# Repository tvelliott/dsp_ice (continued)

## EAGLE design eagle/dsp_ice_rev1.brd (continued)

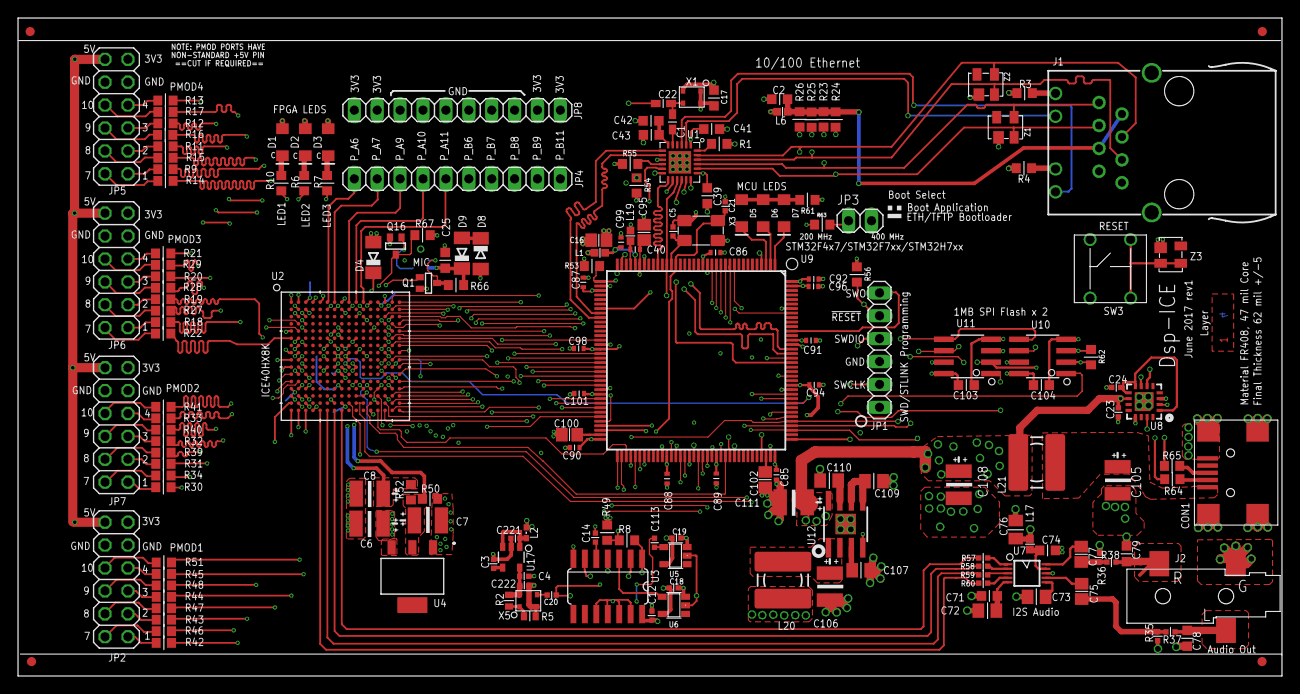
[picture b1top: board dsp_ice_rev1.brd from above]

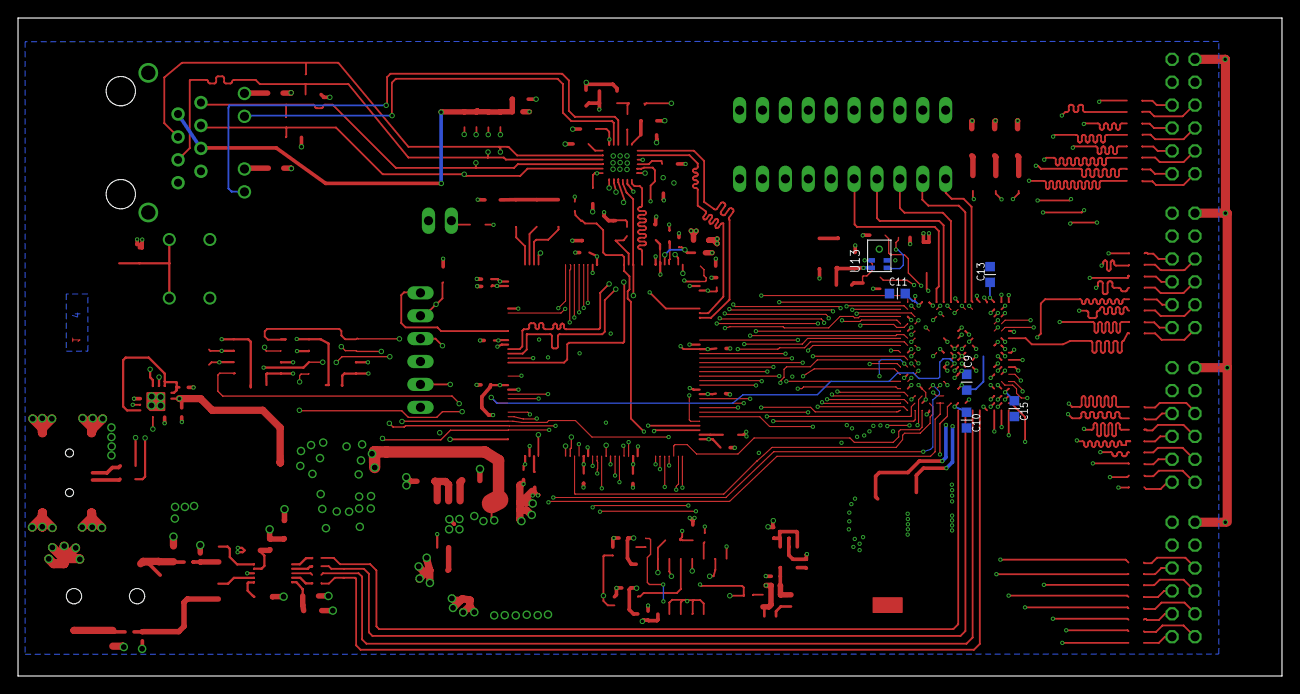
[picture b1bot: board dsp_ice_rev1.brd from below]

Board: 4 copper layers, 140.2 x 73.0 mm, 188 parts (6 on the bottom side), 223 nets.

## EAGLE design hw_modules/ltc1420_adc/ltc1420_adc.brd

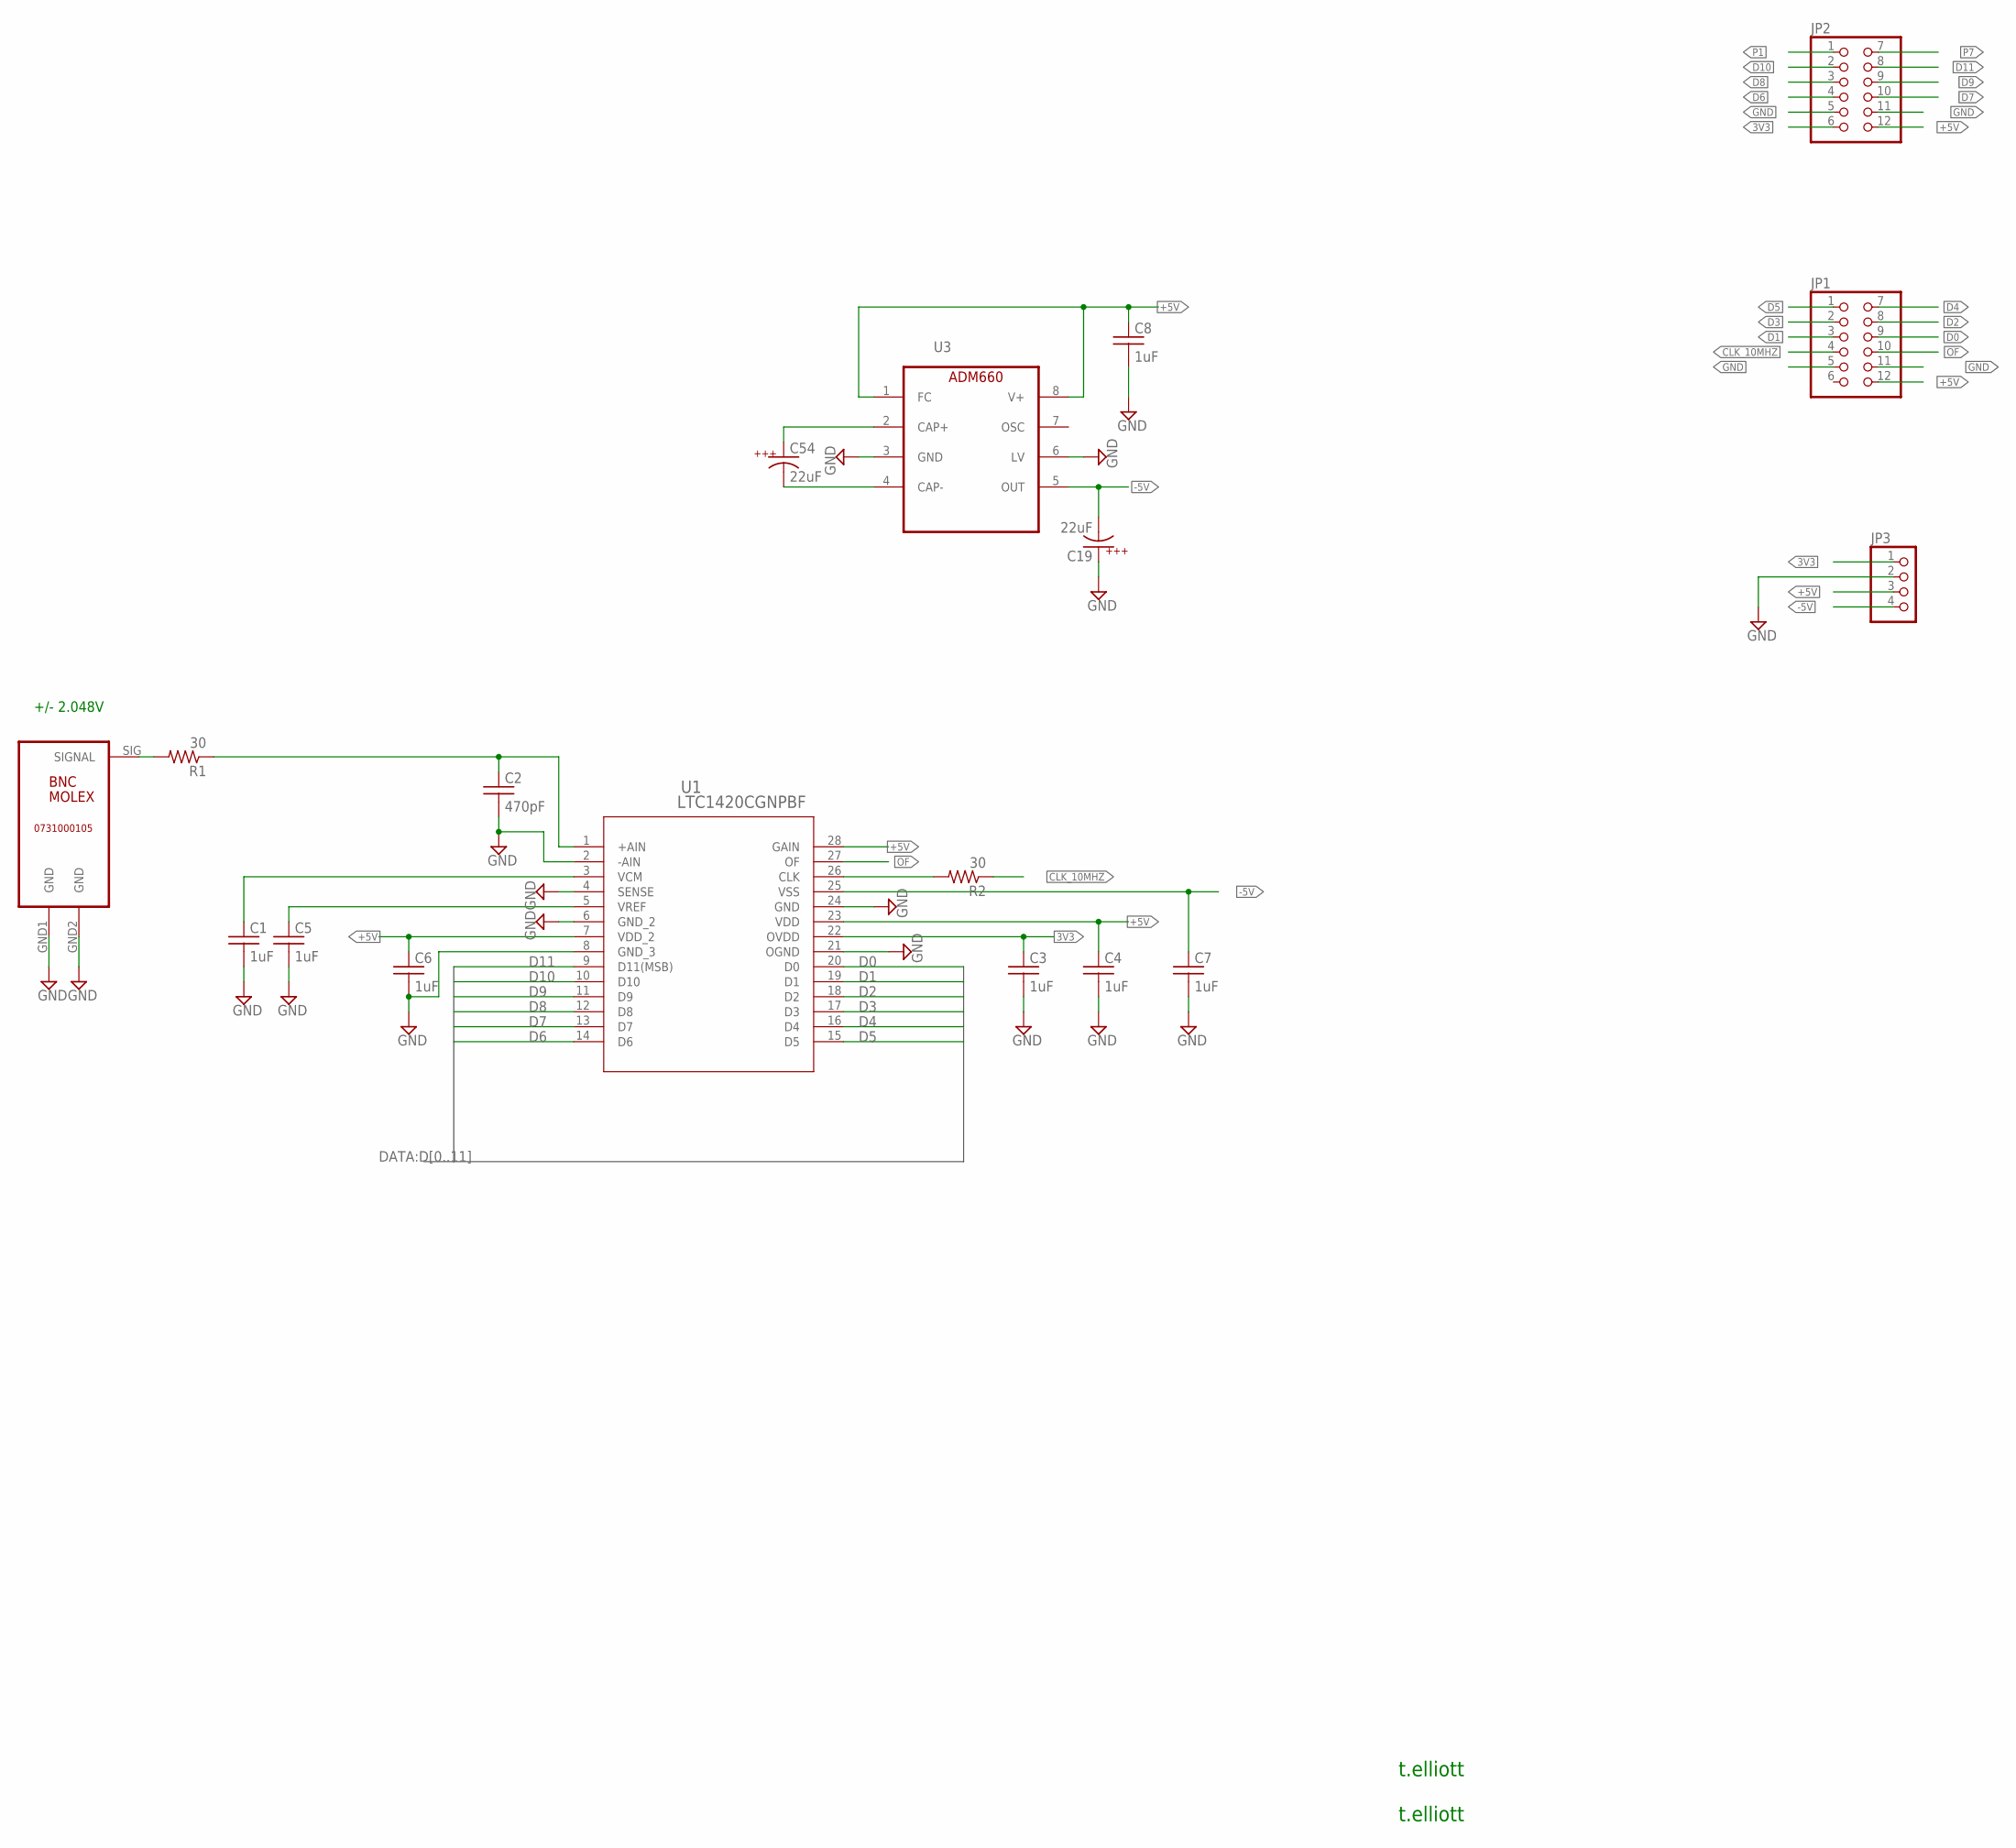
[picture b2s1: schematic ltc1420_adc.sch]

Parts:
C1, C3, C4, C5, C6, C7, C8: 1uF; C0603
C2: 470pF; C0603
C19, C54: 22uF; 1210K
J1: 0731000105_MOLEX_BNC; BNC
JP1, JP2: PINHD-2X6; 2X06
JP3: PINHD-1X4; 1X04
R1, R2: 30; R0402
U1: LTC1420CGNPBF; SSOP-28_GN
U3: ADM660; SO8

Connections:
3V3: C3.1, JP2.6 (11), JP3.1, U1.22 (OVDD)
+5V: C4.1, C6.1, C8.1, JP1.12, JP2.12, JP3.3, U1.7 (VDD_2), U1.23 (VDD), U1.28 (GAIN), U3.1 (FC), U3.8 (V+)
-5V: C7.1, C19.C, JP3.4, U1.25 (VSS), U3.5 (OUT)
CLK_10MHZ: JP1.4 (7), R2.1
D0: JP1.9 (6), U1.20 (D0)
D1: JP1.3 (5), U1.19 (D1)
D2: JP1.8 (4), U1.18 (D2)
D3: JP1.2 (3), U1.17 (D3)
D4: JP1.7 (2), U1.16 (D4)
D5: JP1.1, U1.15 (D5)
D6: JP2.4 (7), U1.14 (D6)
D7: JP2.10 (8), U1.13 (D7)
D8: JP2.3 (5), U1.12 (D8)
D9: JP2.9 (6), U1.11 (D9)
D10: JP2.2 (3), U1.10 (D10)
D11: JP2.8 (4), U1.9 (D11(MSB))
GND: C1.2, C2.2, C3.2, C4.2, C5.2, C6.2, C7.2, C8.2, C19.A, J1.GND1 (GND), J1.GND2 (GND), JP1.5 (9), JP1.11 (10), JP2.5 (9), JP2.11 (10), JP3.2, U1.2 (-AIN), U1.4 (SENSE), U1.6 (GND_2), U1.8 (GND_3), U1.21 (OGND), U1.24 (GND), U3.3 (GND), U3.6 (LV)
unnamed: C2.1, R1.1, U1.1 (+AIN)
unnamed: C1.1, U1.3 (VCM)
unnamed: J1.SIG (SIGNAL), R1.2
unnamed: C5.1, U1.5 (VREF)
unnamed: R2.2, U1.26 (CLK)
unnamed: C54.A, U3.2 (CAP+)
unnamed: C54.C, U3.4 (CAP-)
OF: JP1.10 (8), U1.27 (OF)
P1: JP2.1
P7: JP2.7 (2)

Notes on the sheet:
t.elliott
+/- 2.048V

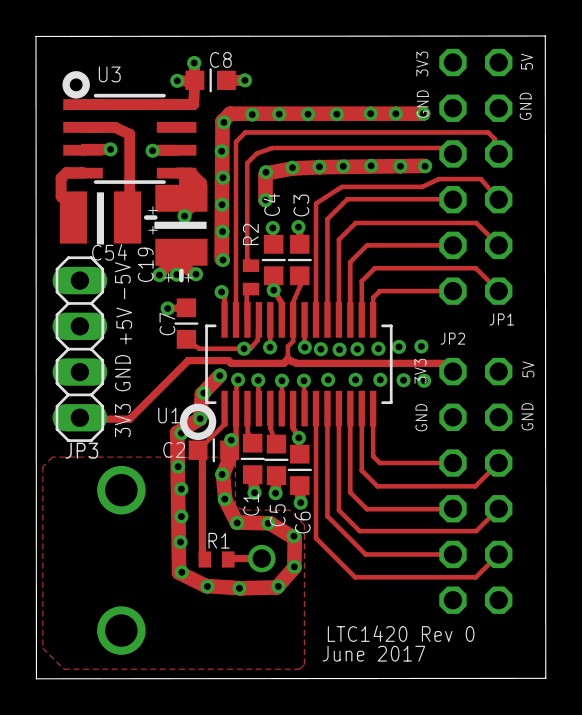
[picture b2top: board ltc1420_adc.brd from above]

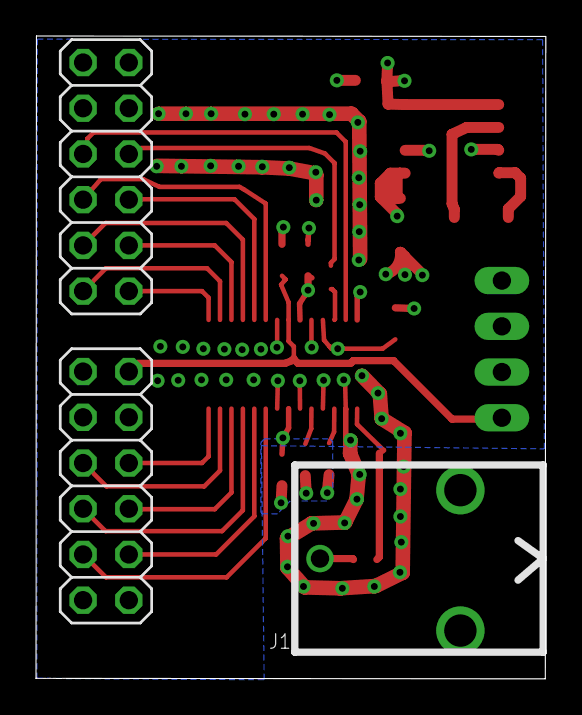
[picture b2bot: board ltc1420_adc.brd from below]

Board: 4 copper layers, 28.3 x 35.7 mm, 18 parts (3 on the bottom side), 25 nets.

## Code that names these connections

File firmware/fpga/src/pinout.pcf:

set_io LED2 A1 
set_io LED3 A2 
set_io LED4 A5 
set_io clk R9 
set_io AUDIO_SDIN T8 
set_io AUDIO_SCLK T7 
set_io AUDIO_LRCLK T6 
set_io AUDIO_MCLK T5 
set_io CBSEL P13
set_io PMOD1_1 P2
set_io PMOD1_2 R2 
set_io PMOD1_3 T1 
set_io PMOD1_4 T3
set_io PMOD1_7 P1
set_io PMOD1_8 R1
set_io PMOD1_9 R3
set_io PMOD1_10 T2
set_io PMOD2_1 K1 
set_io PMOD2_2 L3
set_io PMOD2_3 M2 
set_io PMOD2_4 N3 
set_io PMOD2_7 K3 
set_io PMOD2_8 L1 
set_io PMOD2_9 M1 
set_io PMOD2_10 N2 
set_io PMOD3_1 F2 
set_io PMOD3_2 G3
set_io PMOD3_3 H1 
set_io PMOD3_4 J2 
set_io PMOD3_7 F1 
set_io PMOD3_8 G2 
set_io PMOD3_9 H2 
set_io PMOD3_10 J1 
set_io PMOD4_1 B3 
set_io PMOD4_2 C3 
set_io PMOD4_3 D3 
set_io PMOD4_4 E3 
set_io PMOD4_7 B2 
set_io PMOD4_8 C2 
set_io PMOD4_9 D2 
set_io PMOD4_10 E2 
set_io P_A6 A6 
set_io P_A7 A7 
set_io P_A9 A9 
set_io P_A10 A10 
set_io P_A11 A11 
set_io P_B6 B6 
set_io P_B7 B7 
set_io P_B8 B8 
set_io P_B9 B9 
set_io P_B11 B11 
set_io A0 C16 
set_io A1 T15 
set_io A2 R16 
set_io A3 R15 
set_io A4 P16 
set_io A5 P15 
set_io A6 N16 
set_io A7 M16 
set_io A8 M15 
set_io A9 L16 
set_io A10 T14 
set_io A11 R14  
set_io A12 P14 
set_io A13 L14 
set_io A14 D14 
set_io A15 C14 
set_io D0 D16 
set_io D1 D15 
set_io D2 B16 
set_io D3 B15 
set_io D4 A16 
set_io D5 A15 
set_io D6 E16 
set_io D7 F15 
set_io D8 F16 
set_io D9 G15 
set_io D10 G16 
set_io D11 J15 
set_io D12 J16 
set_io D13 K15 
set_io D14 K16 
set_io D15 T16 
set_io FSMC_NOE F14 
set_io FSMC_NWE H14 
set_io FSMC_NE1 J14 
set_io FSMC_NE4 K14 
set_io FSMC_NL_NADV B14
set_io FPGA_SPI_SCLK R10
set_io FPGA_SPI_MOSI P10
set_io FPGA_SPI_MISO N12
set_io FPGA_SPI_CS T13
set_io FSMC_CLK K9 

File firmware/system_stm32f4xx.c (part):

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   +-------------------+--------------------+------------------+------------------+
   +                       SRAM pins assignment                                   +
   +-------------------+--------------------+------------------+------------------+
   | PD0  <-> FSMC_D2  | PE0  <-> FSMC_NBL0 | PF0  <-> FSMC_A0 | PG0 <-> FSMC_A10 |
   | PD1  <-> FSMC_D3  | PE1  <-> FSMC_NBL1 | PF1  <-> FSMC_A1 | PG1 <-> FSMC_A11 |
   | PD4  <-> FSMC_NOE | PE3  <-> FSMC_A19  | PF2  <-> FSMC_A2 | PG2 <-> FSMC_A12 |
   | PD5  <-> FSMC_NWE | PE4  <-> FSMC_A20  | PF3  <-> FSMC_A3 | PG3 <-> FSMC_A13 |
   | PD8  <-> FSMC_D13 | PE7  <-> FSMC_D4   | PF4  <-> FSMC_A4 | PG4 <-> FSMC_A14 |
   | PD9  <-> FSMC_D14 | PE8  <-> FSMC_D5   | PF5  <-> FSMC_A5 | PG5 <-> FSMC_A15 |
   | PD10 <-> FSMC_D15 | PE9  <-> FSMC_D6   | PF12 <-> FSMC_A6 | PG9 <-> FSMC_NE2 |
   | PD11 <-> FSMC_A16 | PE10 <-> FSMC_D7   | PF13 <-> FSMC_A7 |------------------+
   | PD12 <-> FSMC_A17 | PE11 <-> FSMC_D8   | PF14 <-> FSMC_A8 |
   | PD13 <-> FSMC_A18 | PE12 <-> FSMC_D9   | PF15 <-> FSMC_A9 |
   | PD14 <-> FSMC_D0  | PE13 <-> FSMC_D10  |------------------+
   | PD15 <-> FSMC_D1  | PE14 <-> FSMC_D11  |
   |                   | PE15 <-> FSMC_D12  |
   +-------------------+--------------------+
  */
  /* Enable GPIOD, GPIOE, GPIOF and GPIOG interface clock */
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
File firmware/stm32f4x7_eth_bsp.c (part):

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
  /* ETHERNET pins configuration */
  /* PA
  ETH_RMII_REF_CLK: PA1
  ETH_RMII_MDIO: PA2
  ETH_RMII_MDINT: PA3
  ETH_RMII_CRS_DV: PA7
  */

  /* Configure PA1, PA2, PA3 and PA7*/
  GPIO_InitStructure.GPIO_Pin = GPIO_Pin_1 | GPIO_Pin_2 | GPIO_Pin_7;
  GPIO_InitStructure.GPIO_OType = GPIO_OType_PP;
  GPIO_InitStructure.GPIO_Mode = GPIO_Mode_AF;
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  GPIO_InitStructure.GPIO_Speed = GPIO_Speed_50MHz;
  GPIO_Init(GPIOA, &GPIO_InitStructure);

  /* Connect PA1, PA2, PA3 and PA7 to ethernet module*/
  GPIO_PinAFConfig(GPIOA, GPIO_PinSource1, GPIO_AF_ETH);
  GPIO_PinAFConfig(GPIOA, GPIO_PinSource2, GPIO_AF_ETH);
  //GPIO_PinAFConfig(GPIOA, GPIO_PinSource3, GPIO_AF_ETH);
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

  /* PC
  ETH_RMII_MDC: PC1
  ETH_RMII_RXD0: PC4
  ETH_RMII_RXD1: PC5
  */

  /* Configure PC1, PC4 and PC5*/
  GPIO_InitStructure.GPIO_Pin = GPIO_Pin_1 | GPIO_Pin_4 | GPIO_Pin_5;
  GPIO_InitStructure.GPIO_OType = GPIO_OType_PP;
  GPIO_InitStructure.GPIO_Mode = GPIO_Mode_AF;
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  GPIO_InitStructure.GPIO_Speed = GPIO_Speed_50MHz;
  GPIO_Init(GPIOC, &GPIO_InitStructure);

  /* Connect PC1, PC4 and PC5 to ethernet module*/
  GPIO_PinAFConfig(GPIOC, GPIO_PinSource1, GPIO_AF_ETH);
  GPIO_PinAFConfig(GPIOC, GPIO_PinSource4, GPIO_AF_ETH);
  GPIO_PinAFConfig(GPIOC, GPIO_PinSource5, GPIO_AF_ETH);
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  GPIO_PinLockConfig(GPIOC, GPIO_Pin_5);

  /* PG
  ETH_RMII_TX_EN: PG11
  ETH_RMII_TXD0: PG13
  ETH_RMII_TXD1: PG14
  */

  /* Configure PG14 and PG15*/
  GPIO_InitStructure.GPIO_Pin = GPIO_Pin_11 | GPIO_Pin_13 | GPIO_Pin_14;
  GPIO_InitStructure.GPIO_OType = GPIO_OType_PP;
  GPIO_InitStructure.GPIO_Mode = GPIO_Mode_AF;
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  GPIO_InitStructure.GPIO_Speed = GPIO_Speed_50MHz;
  GPIO_Init(GPIOG, &GPIO_InitStructure);

  /* Connect PG13 and PG15 to ethernet module*/
  GPIO_PinAFConfig(GPIOG, GPIO_PinSource11, GPIO_AF_ETH);
  GPIO_PinAFConfig(GPIOG, GPIO_PinSource13, GPIO_AF_ETH);
  GPIO_PinAFConfig(GPIOG, GPIO_PinSource14, GPIO_AF_ETH);
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  EXTI_InitTypeDef EXTI_InitStructure;
  NVIC_InitTypeDef NVIC_InitStructure;

  /* Enable the INT (PB14) Clock */
  //RCC_AHB1PeriphClockCmd(ETH_LINK_GPIO_CLK, ENABLE);
  RCC_APB2PeriphClockCmd(RCC_APB2Periph_SYSCFG, ENABLE);

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
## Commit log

2017-08-13 fixed header file issue with compling fft / dsp example. added USB/serial test firmware
2017-09-24 added plots of p25 decode in action
2017-09-28 update the readme.md regarding PDM microphone and Cirrus Logic policy
2017-10-03 removed unrelated from readme
2017-10-04 fix buffer overflow in test_adc()
